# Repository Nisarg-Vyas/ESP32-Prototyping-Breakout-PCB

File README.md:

# ESP32 Prototyping & Breakout Board

A custom PCB designed to make ESP32 prototyping easier, faster, and more convenient than working directly on a breadboard or perfboard.

## Overview

When working with ESP32 development boards, the physical form factor can make breadboard prototyping inconvenient. In particular, larger ESP32 boards can occupy a large portion of a breadboard and restrict convenient access to the pins on both sides.

A perfboard can solve some of these problems, but manually wiring a large number of closely spaced GPIO connections is tedious and time-consuming.

This project was created as a reusable PCB-based prototyping platform. The ESP32 is mounted on the board while its pins are brought out to multiple accessible header rows. The board also provides dedicated power and ground connections and supports more than one ESP32 development-board form factor.

The goal is not to replace a breadboard for every project, but to make repeated ESP32 prototyping cleaner and faster.

## Motivation

The project started from a simple practical problem:

- A larger ESP32 development board does not leave convenient access to both sides of a breadboard.
- Connecting peripherals to both sides of the ESP32 can therefore become awkward.
- Dense adjacent GPIO connections on a perfboard require a lot of manual soldering.
- A custom PCB provides a repeatable layout that can be reused across multiple ESP32 prototypes.
- Since the board was already being designed for the larger ESP32 form factor, the layout was made compatible with a smaller ESP32 board as well.

### Breadboard vs. Custom PCB

The photographs in `Images/` show the motivation for the design.

The larger ESP32 board occupies a significant area of the breadboard, limiting convenient access to the surrounding rows. The custom PCB instead places the ESP32 in the center and distributes its connections across accessible header rows.

## Features

- ESP32 pin breakout through multiple 2.54 mm header rows
- Dedicated GND connections
- Dedicated 5 V connections
- Dedicated 3.3 V connections
- USB Type-C input circuit on the PCB
- USB Type-C CC resistors
- AMS1117-3.3 V linear regulator
- Regulator input/output capacitors
- 5 V indicator LED
- 3.3 V indicator LED
- Separate test LED
- Through-hole headers with SMD supporting circuitry
- Designed for multiple ESP32 development-board form factors
- Compact custom PCB: approximately **87.62 mm × 70 mm**
- Final PCB layout completed with no unrouted connections in KiCad

> **Note:** The USB Type-C connector itself has not yet been sourced by me, so it is **not soldered onto the current physical PCB**. The connector footprint and supporting circuitry are present in the PCB design, but the current prototype does not have the Type-C connector populated.

## Hardware Design

### Block Diagram

```text
                    USB Type-C
                        |
                        v
                    5 V Rail
                   /       \
                  /         \
             5 V LED      AMS1117-3.3
                              |
                              v
                         3.3 V Rail
                              |
                              v
                           ESP32
                              |
             +----------------+----------------+
             |                |                |
          GPIO Headers     GND Headers     Power Headers
```

### Schematic

The schematic is divided into:

- USB Type-C input
- 3.3 V regulation
- Indicator LEDs
- ESP32 header connections
- Power and ground rails

## PCB Design

The board was designed in **KiCad**.

The layout contains multiple parallel ESP32 header rows so that the ESP32 connections remain accessible while the ESP32 is mounted on the board.

The final PCB has:

- Board size: **87.62 mm × 70 mm**
- 2.54 mm header spacing
- SMD power/regulator circuitry
- Through-hole ESP32/header connections
- USB Type-C footprint and supporting circuit
- Dedicated power and ground access

## Physical Board

### PCB without ESP32

The board exposes the ESP32 connections through the surrounding header rows.

### PCB with larger ESP32

The larger ESP32 development board fits into the central position while leaving the breakout headers accessible.

### PCB with smaller ESP32

The board was also designed to accommodate a smaller ESP32 development-board form factor.

### ESP32 on a Breadboard

This comparison illustrates the original motivation for the project: using a larger ESP32 board directly on a breadboard can make access to both sides inconvenient.

### Back of the PCB

The back side shows the routing and the first-board markings:

> PCB #1 — 12+ hours  
> NV • ESP32 Proto v1 • 08/07/2026  
> May the traces be with you

## Pinout

The header arrangement uses the **ESP32 module pin numbers** used in the KiCad schematic.

The pinout documentation is available in:

[`Documentation/Pinout.md`](Documentation/Pinout.md)

The four 19-pin breakout rows are arranged as paired groups:

- One row exposes ESP32 module pins **1–19**
- The paired row exposes ESP32 module pins **20–38**

This arrangement is repeated for the supported ESP32 board positions.

> The schematic uses the module's physical pin numbers (1–38). It does not label these connections with GPIO names, so the pinout document intentionally preserves the numbering used by the design rather than introducing a separate GPIO mapping.

## Design Files

The `KiCad/` directory contains the editable KiCad project:

```text
KiCad/
├── pcb_esp32_v1.kicad_pro
├── pcb_esp32_v1.kicad_sch
└── pcb_esp32_v1.kicad_pcb
```

### Fabrication Files

The `Fabrication/` directory is intended for files required to reproduce the physical board:

```text
Fabrication/
├── final_gerbers.zip
└── bom.csv
```

### Gerbers

Gerber files describe the PCB layers and board geometry used by a PCB manufacturer to fabricate the bare PCB.

### Bill of Materials (BOM)

The BOM lists the components required to assemble the board, including their references, values, footprints, and quantities.

A CSV BOM can be placed in:

```text
Fabrication/bom.csv
```

## Repository Structure

```text
ESP32-Prototyping-Breakout/
│
├── README.md
├── LICENSE
├── .gitignore
│
├── KiCad/
│   ├── pcb_esp32_v1.kicad_pro
│   ├── pcb_esp32_v1.kicad_sch
│   └── pcb_esp32_v1.kicad_pcb
│
├── Fabrication/
│   ├── final_gerbers.zip
│   └── bom.csv
│
├── Documentation/
│   └── Pinout.md
│
└── Images/
    ├── 01_esp32_on_breadboard.jpg
    ├── 02_pcb_with_esp32_form_factor_1.jpg
    ├── 03_pcb_with_esp32_form_factor_2.jpg
    ├── 04_large_esp32_on_breadboard.jpg
    ├── 05_pcb_front.jpg
    ├── 06_pcb_back.jpg
    ├── 07_pcb_layout.png
    └── 08_schematic.png
```

## Project Status

**Version:** v1

This is a personal prototype and my first custom PCB design.

The physical board was fabricated and assembled for ESP32 prototyping and experimentation.

The current physical prototype has the USB Type-C connector footprint unpopulated because the connector has not yet been sourced.

The board was designed as a practical development aid rather than as a production-ready commercial board.

## Future Improvements

Possible improvements for a future revision include:

- Populate and validate the USB Type-C connector
- More clearly standardized pin labels
- Additional protection circuitry
- Improved mechanical mounting options
- Additional prototyping headers
- Further optimization of board size and routing
- Additional ESP32 development-board compatibility

## Tools

- **KiCad** — schematic capture and PCB design
- **PCB fabrication** — custom manufactured PCB
- **ESP32 development boards** — hardware validation and prototyping

## License

This hardware design and associated documentation are released under the MIT License. See [`LICENSE`](LICENSE) for details.

## Author

**Nisarg Vyas**

Computer Science & Engineering

---

> *PCB #1 — 12+ hours*  
> *May the traces be with you.*

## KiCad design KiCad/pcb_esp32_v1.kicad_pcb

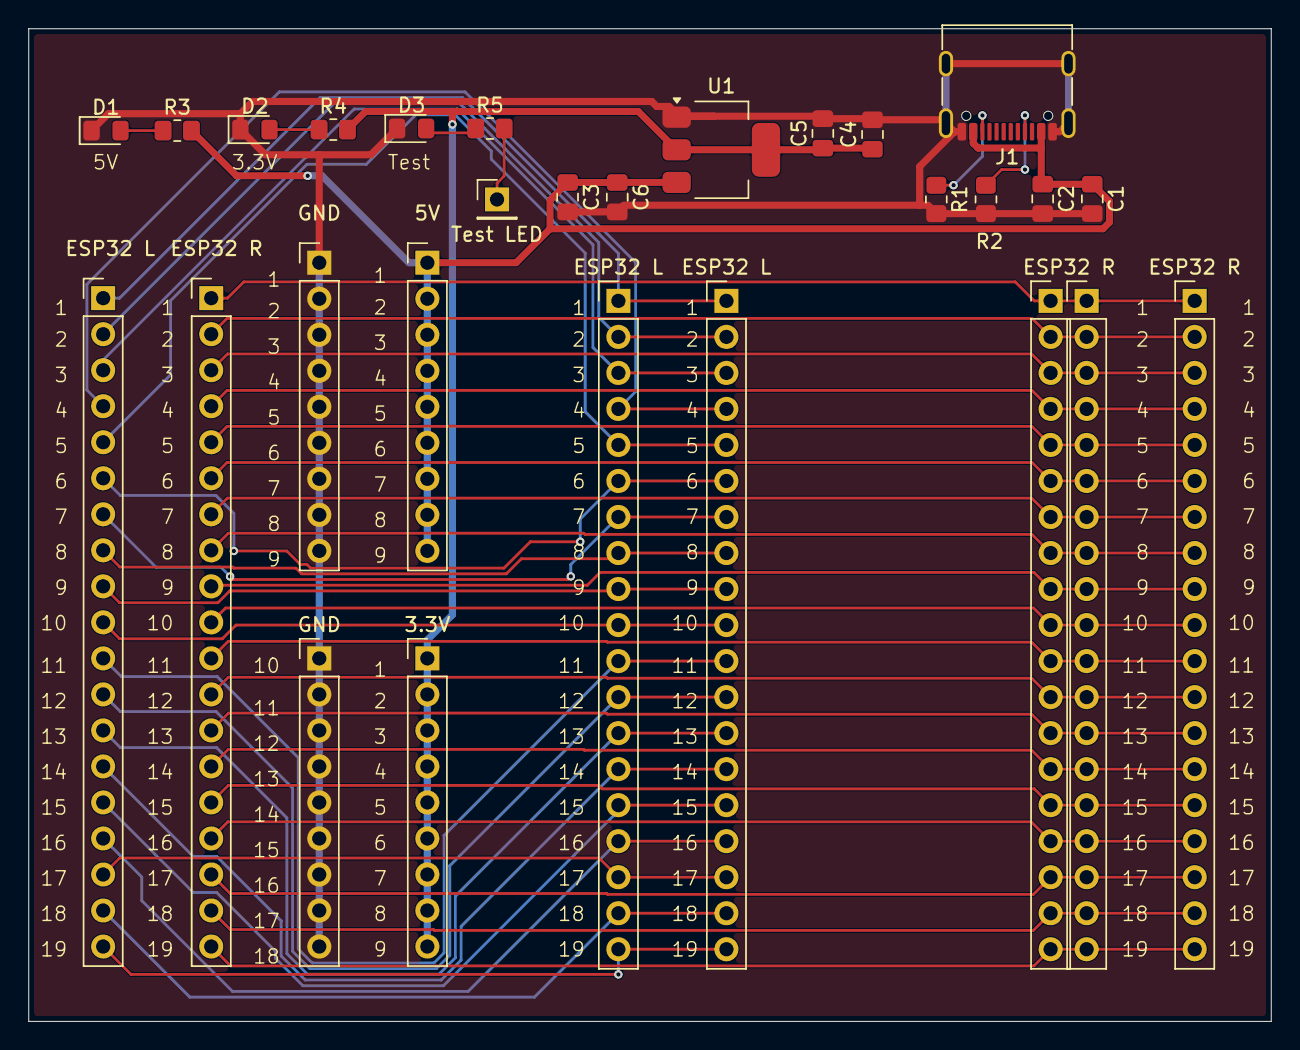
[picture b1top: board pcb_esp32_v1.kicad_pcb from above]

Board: 2 copper layers, 87.6 x 70.0 mm, 28 parts (0 on the bottom side), 47 nets.

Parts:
3.3V: 3.3V Rail; PinHeader_1x09_P2.54mm_Vertical
5V: 5V Rail; PinHeader_1x09_P2.54mm_Vertical
C1, C3: 10uF; C_0805_2012Metric_Pad1.18x1.45mm_HandSolder
C2, C5, C6: 100nF; C_0805_2012Metric_Pad1.18x1.45mm_HandSolder
C4: 22uF; C_0805_2012Metric_Pad1.18x1.45mm_HandSolder
D1, D2, D3: LED; LED_0805_2012Metric_Pad1.15x1.40mm_HandSolder
ESP32 L: ESP32 Rail1L; PinHeader_1x19_P2.54mm_Vertical
ESP32 L#2: ESP32 L; PinHeader_1x19_P2.54mm_Vertical
ESP32 L#3: ESP32 Rail2L; PinHeader_1x19_P2.54mm_Vertical
ESP32 R: ESP32 R; PinHeader_1x19_P2.54mm_Vertical
ESP32 R#2: ESP32 Rail1R; PinHeader_1x19_P2.54mm_Vertical
ESP32 R#3: ESP32 Rail2R; PinHeader_1x19_P2.54mm_Vertical
GND: GND Rail; PinHeader_1x09_P2.54mm_Vertical
GND#2: GND Rail; PinHeader_1x09_P2.54mm_Vertical
J1: USB_C_Receptacle_USB2.0_16P; USB_C_Receptacle_G-Switch_GT-USB-7010ASV
J3: ESP32 R; PinHeader_1x19_P2.54mm_Vertical
R1, R2: 5.1k; R_0805_2012Metric_Pad1.20x1.40mm_HandSolder
R3, R4, R5: 1k; R_0805_2012Metric_Pad1.20x1.40mm_HandSolder
Test LED: Test_LED; PinHeader_1x01_P2.54mm_Vertical
U1: AMS1117-3.3; SOT-223-3_TabPin2

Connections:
/1: ESP32 L.1, ESP32 L#2.1, ESP32 L#3.1
/2: ESP32 L.2, ESP32 L#2.2, ESP32 L#3.2
/3: ESP32 L.3, ESP32 L#2.3, ESP32 L#3.3
/4: ESP32 L.4, ESP32 L#2.4, ESP32 L#3.4
/5: ESP32 L.5, ESP32 L#2.5, ESP32 L#3.5
/6: ESP32 L.6, ESP32 L#2.6, ESP32 L#3.6
/7: ESP32 L.7, ESP32 L#2.7, ESP32 L#3.7
/8: ESP32 L.8, ESP32 L#2.8, ESP32 L#3.8
/9: ESP32 L.9, ESP32 L#2.9, ESP32 L#3.9
/10: ESP32 L.10, ESP32 L#2.10, ESP32 L#3.10
/11: ESP32 L.11, ESP32 L#2.11, ESP32 L#3.11
/12: ESP32 L.12, ESP32 L#2.12, ESP32 L#3.12
/13: ESP32 L.13, ESP32 L#2.13, ESP32 L#3.13
/14: ESP32 L.14, ESP32 L#2.14, ESP32 L#3.14
/15: ESP32 L.15, ESP32 L#2.15, ESP32 L#3.15
/16: ESP32 L.16, ESP32 L#2.16, ESP32 L#3.16
/17: ESP32 L.17, ESP32 L#2.17, ESP32 L#3.17
/18: ESP32 L.18, ESP32 L#2.18, ESP32 L#3.18
/19: ESP32 L.19, ESP32 L#2.19, ESP32 L#3.19
/20: ESP32 R.19, ESP32 R#2.19, ESP32 R#3.19, J3.19
/21: ESP32 R.18, ESP32 R#2.18, ESP32 R#3.18, J3.18
/22: ESP32 R.17, ESP32 R#2.17, ESP32 R#3.17, J3.17
/23: ESP32 R.16, ESP32 R#2.16, ESP32 R#3.16, J3.16
/24: ESP32 R.15, ESP32 R#2.15, ESP32 R#3.15, J3.15
/25: ESP32 R.14, ESP32 R#2.14, ESP32 R#3.14, J3.14
/26: ESP32 R.13, ESP32 R#2.13, ESP32 R#3.13, J3.13
/27: ESP32 R.12, ESP32 R#2.12, ESP32 R#3.12, J3.12
/28: ESP32 R.11, ESP32 R#2.11, ESP32 R#3.11, J3.11
/29: ESP32 R.10, ESP32 R#2.10, ESP32 R#3.10, J3.10
/30: ESP32 R.9, ESP32 R#2.9, ESP32 R#3.9, J3.9
/31: ESP32 R.8, ESP32 R#2.8, ESP32 R#3.8, J3.8
/32: ESP32 R.7, ESP32 R#2.7, ESP32 R#3.7, J3.7
/33: ESP32 R.6, ESP32 R#2.6, ESP32 R#3.6, J3.6
/34: ESP32 R.5, ESP32 R#2.5, ESP32 R#3.5, J3.5
/35: ESP32 R.4, ESP32 R#2.4, ESP32 R#3.4, J3.4
/36: ESP32 R.3, ESP32 R#2.3, ESP32 R#3.3, J3.3
/37: ESP32 R.2, ESP32 R#2.2, ESP32 R#3.2, J3.2
/38: ESP32 R.1, ESP32 R#2.1, ESP32 R#3.1, J3.1
/+3.3V_BOARD: 3.3V.1, 3.3V.2, 3.3V.3, 3.3V.4, 3.3V.5, 3.3V.6, 3.3V.7, 3.3V.8, 3.3V.9, C4.1, C5.1, R4.2, U1.2 (VO)
/+5V_BOARD: 5V.1, 5V.2, 5V.3, 5V.4, 5V.5, 5V.6, 5V.7, 5V.8, 5V.9, C1.1, C2.1, C3.1, C6.1, J1.A4 (VBUS), J1.A9 (VBUS), J1.B4 (VBUS), J1.B9 (VBUS), R3.2, U1.3 (VI)
GND: C1.2, C2.2, C3.2, C4.2, C5.2, C6.2, D1.1 (K), D2.1 (K), D3.1 (K), GND.1, GND.2, GND.3, GND.4, GND.5, GND.6, GND.7, GND.8, GND.9, GND#2.1, GND#2.2, GND#2.3, GND#2.4, GND#2.5, GND#2.6, GND#2.7, GND#2.8, GND#2.9, J1.A1 (GND), J1.A12 (GND), J1.B1 (GND), J1.B12 (GND), J1.SH (SHIELD), R1.2, R2.2, U1.1 (GND)
unnamed: D1.2 (A), R3.1
unnamed: D2.2 (A), R4.1
unnamed: D3.2 (A), R5.1
unnamed: J1.A5 (CC1), R2.1
unnamed: J1.B5 (CC2), R1.1
unnamed: R5.2, Test LED.1 (Pin_1_1)
